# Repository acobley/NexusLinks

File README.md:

View this project on [CADLAB.io](https://cadlab.io/node/804). 

# NexusLinks
## Based on a design by Mutable Instruments: https://mutable-instruments.net/modules/links/

Olivier Gillet ol.gillet@gmail.com

released under a cc-by-sa-3.0 license https://creativecommons.org/licenses/by-sa/3.0/

This version Andy C andy@r2-dvd.org

Changes:

  Removed 2:2 section
  
  Increased input and outputs to 4:1 and 1:4
  
  Changed packaging of chips for easier construction
  
  Changed orientation of sockets to bottom side of the board.

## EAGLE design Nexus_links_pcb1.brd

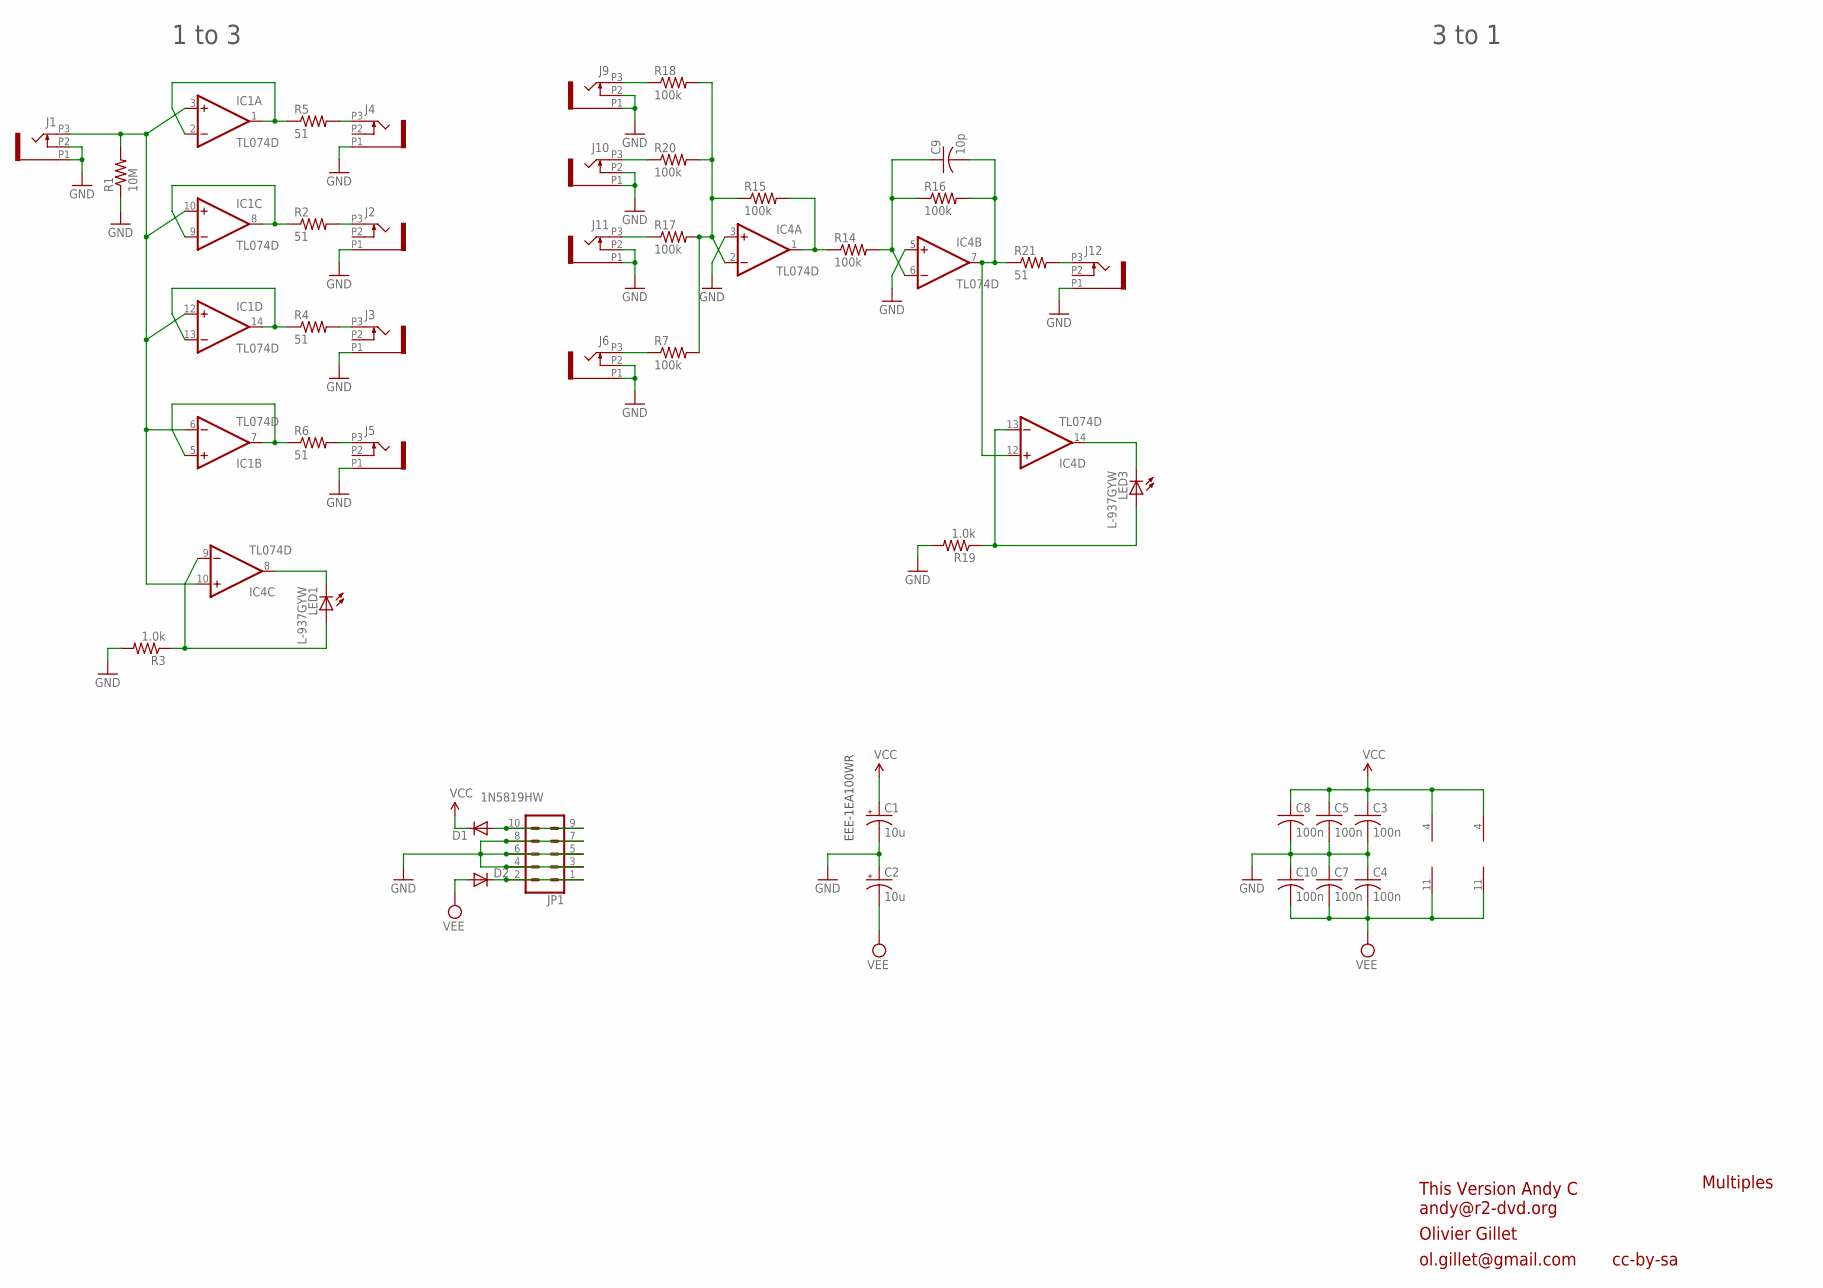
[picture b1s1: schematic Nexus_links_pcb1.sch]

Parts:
C1, C2: 10u; PANASONIC_A
C3, C4, C5, C7, C8, C10: 100n; C0603
C9: 10p; C0603
D1, D2: 1N5819HW; SOD123
IC1, IC4: TL074D; SO14
J1, J2, J3, J4, J5, J6, J9, J10, J11, J12: PJ301_THONKICONN6; WQP_PJ_301M6
JP1: CONN_05X2SHD; 2X5-SHROUDED
LED1, LED3: L-937GYW; LED3MM
R1: 10M; R0603
R2, R4, R5, R6, R21: 51; R0603
R3, R19: 1.0k; R0603
R7, R14, R15, R16, R17, R18, R20: 100k; R0603

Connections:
GND: C1.-, C2.+, C3.2, C4.1, C5.2, C7.1, C8.2, C10.1, IC4.3 (+IN), IC4.5 (+IN), J1.P1 (1), J1.P2 (2), J2.P1 (1), J3.P1 (1), J4.P1 (1), J5.P1 (1), J6.P1 (1), J6.P2 (2), J9.P1 (1), J9.P2 (2), J10.P1 (1), J10.P2 (2), J11.P1 (1), J11.P2 (2), J12.P1 (1), JP1.3, JP1.4, JP1.5, JP1.6, JP1.7, JP1.8, R1.1, R3.2, R19.2
unnamed: IC1.5 (+IN), IC1.7 (OUT), R6.1
unnamed: J11.P3 (3), R17.1
unnamed: IC1.1 (OUT), IC1.2 (-IN), R5.1
unnamed: IC1.8 (OUT), IC1.9 (-IN), R2.1
unnamed: IC1.13 (-IN), IC1.14 (OUT), R4.1
unnamed: D2.C, JP1.1, JP1.2
unnamed: IC1.3 (+IN), IC1.6 (-IN), IC1.10 (+IN), IC1.12 (+IN), IC4.10 (+IN), J1.P3 (3), R1.2
unnamed: IC4.8 (OUT), LED1.K (C)
unnamed: J10.P3 (3), R20.1
unnamed: J6.P3 (3), R7.1
unnamed: J4.P3 (3), R5.2
unnamed: J2.P3 (3), R2.2
unnamed: J3.P3 (3), R4.2
unnamed: J5.P3 (3), R6.2
unnamed: C9.2, IC4.7 (OUT), IC4.12 (+IN), R16.2, R21.1
unnamed: IC4.13 (-IN), LED3.A, R19.1
unnamed: D1.A, JP1.9, JP1.10
unnamed: IC4.9 (-IN), LED1.A, R3.1
unnamed: J9.P3 (3), R18.1
unnamed: J12.P3 (3), R21.2
unnamed: IC4.2 (-IN), R7.2, R15.1, R17.2, R18.2, R20.2
unnamed: IC4.1 (OUT), R14.1, R15.2
unnamed: C9.1, IC4.6 (-IN), R14.2, R16.1
unnamed: IC4.14 (OUT), LED3.K (C)
VCC: C1.+, C3.1, C5.1, C8.1, D1.C, IC1.4 (V+), IC4.4 (V+)
VEE: C2.-, C4.2, C7.2, C10.2, D2.A, IC1.11 (V-), IC4.11 (V-)

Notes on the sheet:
cc-by-sa
Olivier Gillet
ol.gillet@gmail.com
Multiples
1 to 3
3 to 1
EEE-1EA100WR
This Version Andy C andy@r2-dvd.org

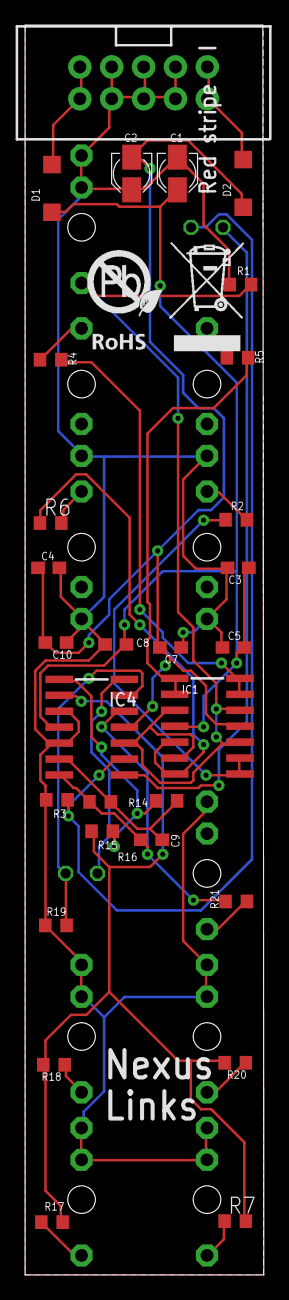
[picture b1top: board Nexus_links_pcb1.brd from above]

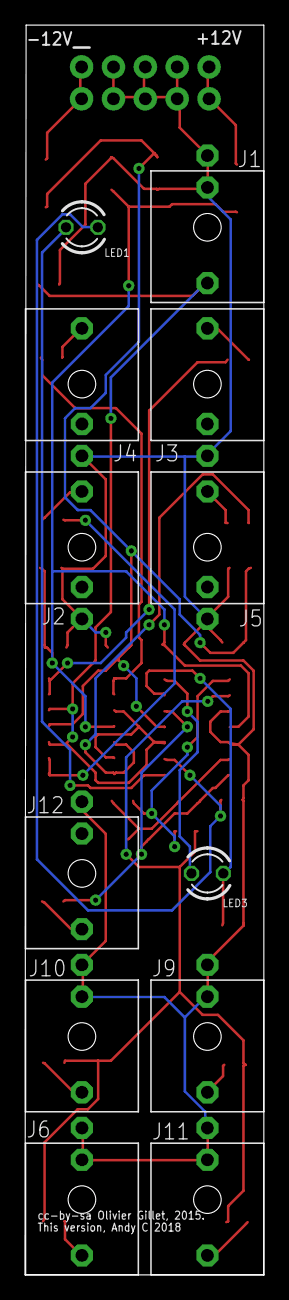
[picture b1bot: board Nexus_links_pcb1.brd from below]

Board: 2 copper layers, 19.0 x 99.6 mm, 42 parts (12 on the bottom side), 27 nets.

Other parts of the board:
U$2: ROHS

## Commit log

2018-03-30 Backlink to CADLAB.io has been added.
2018-03-30 Tidy Layers
2018-03-31 Fixed power connector
2018-03-31 Added ground plane
2018-03-31 first PCB
2018-03-31 Added panel cutout
2018-04-04 updated Panel file
2018-04-04 updated mounting holes
2018-12-09 updated in december
2018-12-09 updated values to precission adder

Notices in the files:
Nexus_links_pcb1.brd:
cc-by-sa Olivier Gillet, 2015.
parts and their libraries:
SparkFun-Connectors: Licensing: Creative Commons ShareAlike 4.0 International - https://creativecommons.org/licenses/by-sa/4.0
